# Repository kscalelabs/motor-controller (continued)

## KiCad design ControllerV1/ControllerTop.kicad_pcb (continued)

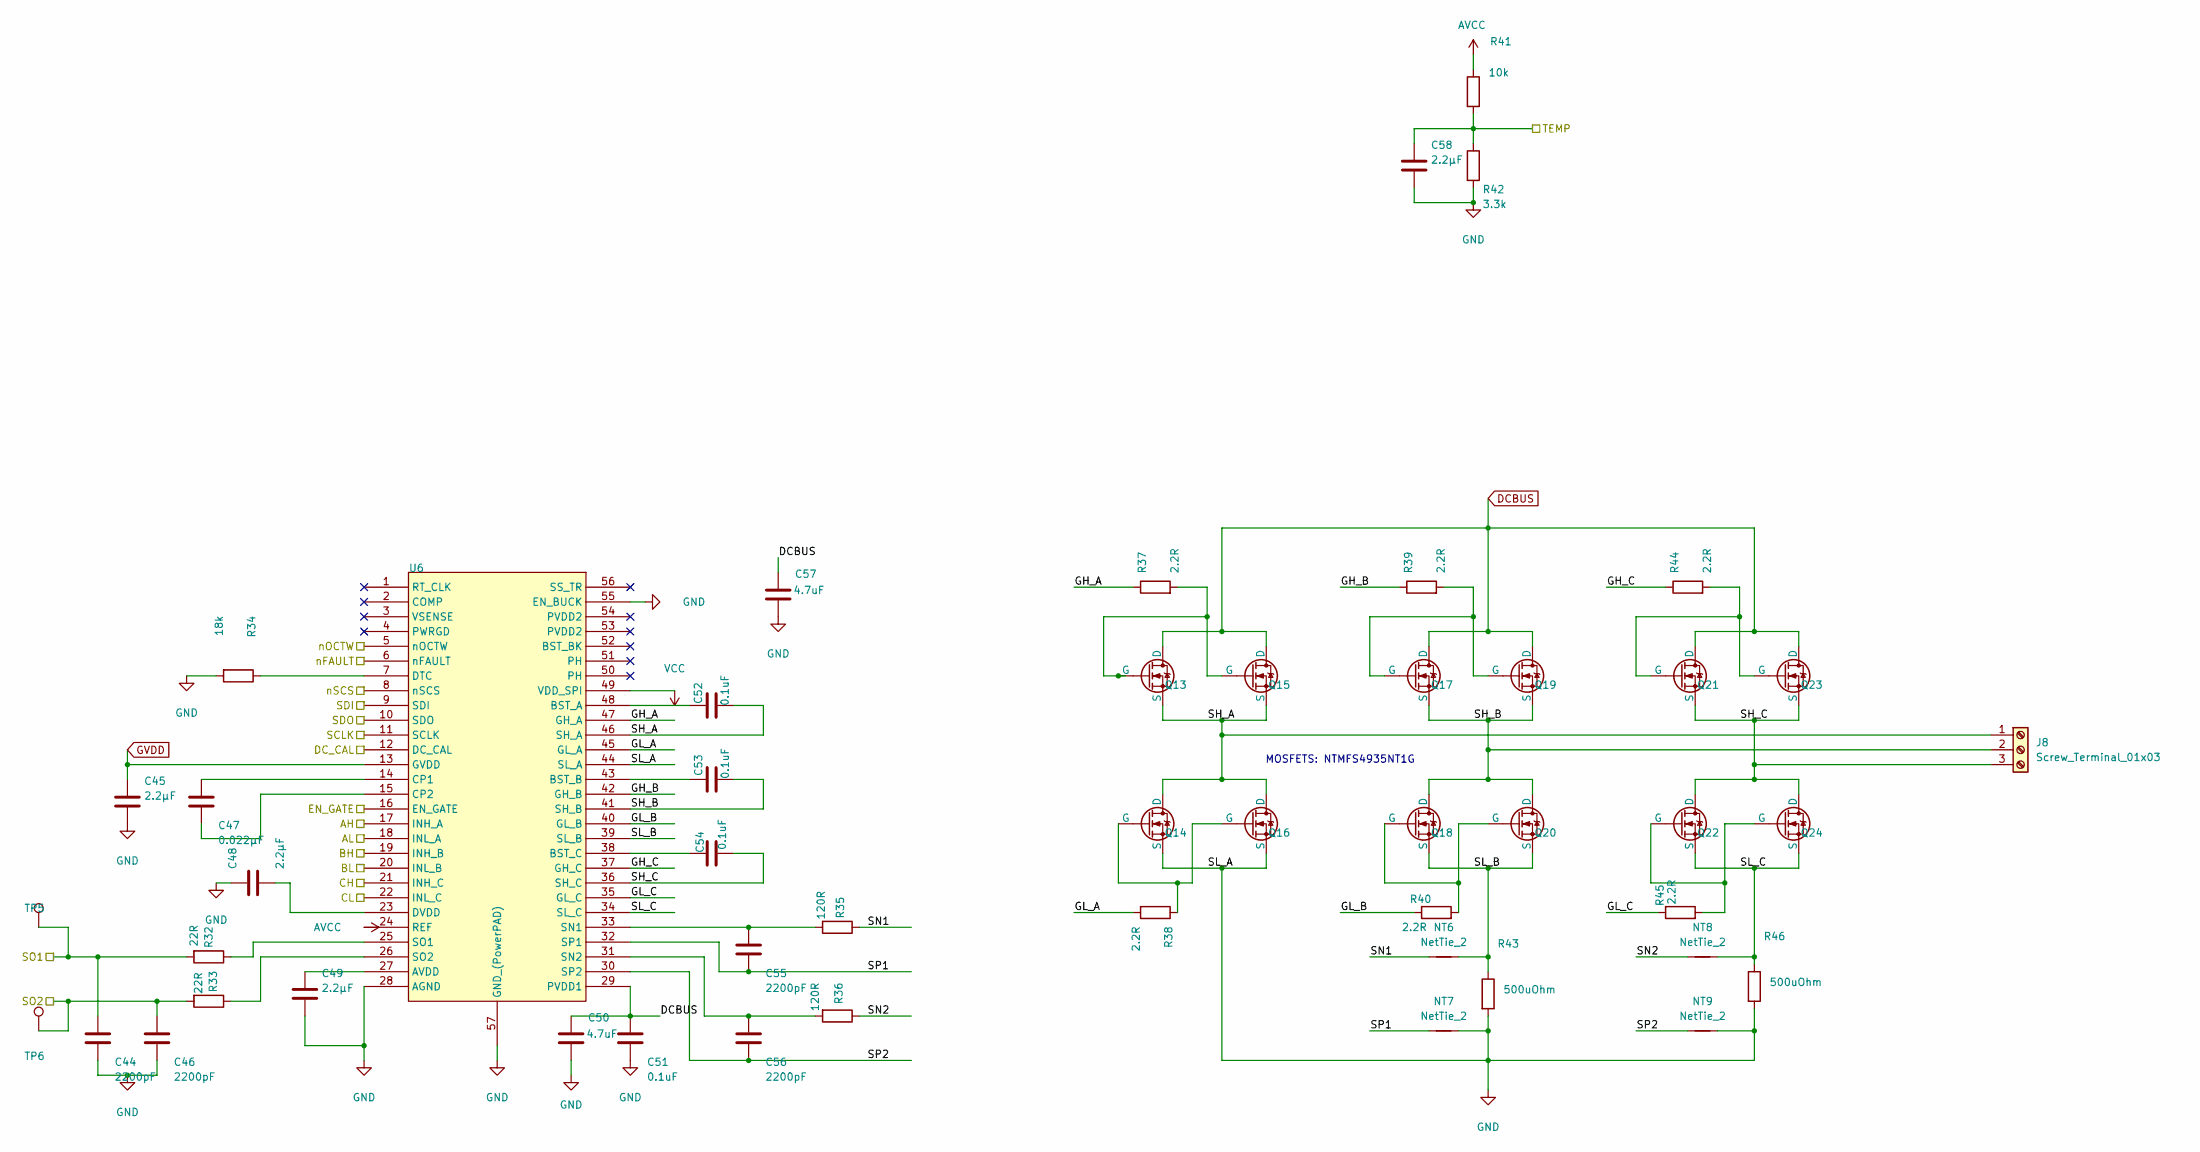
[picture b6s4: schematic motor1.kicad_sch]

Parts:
C44, C46, C55, C56: 2200pF; C_0603_1608Metric; TOLERANCE ±5%; VOLTAGE - RATED 50V; PART STATUS Active
C45, C48, C49, C58: 2.2µF; C_0603_1608Metric; TOLERANCE ±10%; VOLTAGE - RATED 16V; MANUFACTURER PART NUMBER GRM188R61C225KE15D
C47: 0.022µF; C_0603_1608Metric; TOLERANCE ±10%; VOLTAGE - RATED 50V; MANUFACTURER PART NUMBER GRM188R71H223KA01D
C50, C57: 4.7uF; C_0805_2012Metric; TOLERANCE ±10%; VOLTAGE - RATED 35V; PART STATUS Active
C51, C52, C53, C54: 0.1uF; C_0603_1608Metric; TOLERANCE ±10%; VOLTAGE - RATED 50V; MANUFACTURER PART NUMBER GRM188R71H104KA93D
J8: Screw_Terminal_01x03; TerminalBlock_MetzConnect_Type011_RT05503HBWC_1x03_P5.00mm_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
NT6, NT7, NT8, NT9: NetTie_2; NetTie-2_SMD_Pad0.5mm
Q13, Q14, Q16, Q17, Q18, Q20, Q21, Q22, Q24: ONSemi_SO-8FL_488AA; DRIVE VOLTAGE (MAX RDS 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 4.5V, 10V; PART STATUS Active
Q15, Q19, Q23: FILL_FOOTPRINT; ONSemi_SO-8FL_488AA; DRIVE VOLTAGE (MAX RDS 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 4.5V, 10V; PART STATUS Active
R32, R33: 22R; R_0603_1608Metric; TOLERANCE ±1%; MANUFACTURER PART NUMBER RC0603FR-0722RL
R34: 18k; R_0603_1608Metric; TOLERANCE ±1%; MANUFACTURER PART NUMBER RC0603FR-0718KL
R35, R36: 120R; R_0603_1608Metric; TOLERANCE ±1%; MANUFACTURER PART NUMBER RC0603FR-07120RL
R37, R38, R39, R40, R44, R45: 2.2R; R_0603_1608Metric; TOLERANCE ±1%; MANUFACTURER PART NUMBER RC0603FR-072R2L
R41: 10k; R_0402_1005Metric
R42: 3.3k; R_0603_1608Metric; TOLERANCE ±1%; MANUFACTURER PART NUMBER RC0603FR-073K3L
R43, R46: 500uOhm; R_2512_6332Metric; TOLERANCE ±1%; PART STATUS Active
TP5, TP6: TESTPOINT; TestPoint_Pad_1.0x1.0mm
U6: HTSSOP-56-1EP_6.1x14mm_P0.5mm_EP3.61x6.35mm

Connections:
/EN_GATE: U6.16 (EN_GATE); also elsewhere on the board
/M1_AH: U6.17 (INH_A); also elsewhere on the board
/M1_AL: U6.18 (INL_A); also elsewhere on the board
/M1_BH: U6.19 (INH_B); also elsewhere on the board
/M1_BL: U6.20 (INL_B); also elsewhere on the board
/M1_CH: U6.21 (INH_C); also elsewhere on the board
/M1_CL: U6.22 (INL_C); also elsewhere on the board
/M1_DC_CAL: U6.12 (DC_CAL); also elsewhere on the board
/M1_NCS: U6.8 (nSCS); also elsewhere on the board
/M1_SO1: C44.1, R32.2, TP5.1; also elsewhere on the board
/M1_SO2: C46.1, R33.2, TP6.1; also elsewhere on the board
/M1_TEMP: C58.1, R41.2, R42.1, U6.5 (nOCTW); also elsewhere on the board
/Motor 1/GH_A: R37.1, U6.47 (GH_A)
/Motor 1/GH_B: R39.1, U6.42 (GH_B)
/Motor 1/GH_C: R44.1, U6.37 (GH_C)
/Motor 1/GL_A: R38.2, U6.45 (GL_A)
/Motor 1/GL_B: R40.1, U6.40 (GL_B)
/Motor 1/GL_C: R45.1, U6.35 (GL_C)
/Motor 1/SH_A: C52.1, J8.1, Q13.1 (S), Q14.5 (D), Q15.1 (S), Q16.5 (D), U6.46 (SH_A)
/Motor 1/SH_B: C53.2, J8.2, Q17.1 (S), Q18.5 (D), Q19.1 (S), Q20.5 (D), U6.41 (SH_B)
/Motor 1/SH_C: C54.2, J8.3, Q21.1 (S), Q22.5 (D), Q23.1 (S), Q24.5 (D), U6.36 (SH_C)
/Motor 1/SL_B: NT6.2, Q18.1 (S), Q20.1 (S), R43.1, U6.39 (SL_B)
/Motor 1/SL_C: NT8.2, Q22.1 (S), Q24.1 (S), R46.1, U6.34 (SL_C)
/Motor 1/SN1: NT6.1, R35.1
/Motor 1/SN2: NT8.1, R36.1
/Motor 1/SP1: C55.2, NT7.1, U6.32 (SP1)
/Motor 1/SP2: C56.2, NT9.1, U6.30 (SP2)
/SPI_MISO: U6.10 (SDO); also elsewhere on the board
/SPI_MOSI: U6.9 (SDI); also elsewhere on the board
/SPI_SCK: U6.11 (SCLK); also elsewhere on the board
/nFAULT: U6.6 (nFAULT); also elsewhere on the board
AVCC: R41.1, U6.24 (REF); also elsewhere on the board
DCBUS: C50.1, C51.1, C57.1, Q13.5 (D), Q15.5 (D), Q17.5 (D), Q19.5 (D), Q21.5 (D), Q23.5 (D), U6.29 (PVDD1); also elsewhere on the board
GND: C44.2, C45.2, C46.2, C48.1, C49.2, C50.2, C51.2, C57.2, C58.2, NT7.2, NT9.2, Q14.1 (S), Q16.1 (S), R34.2, R42.2, R43.2, R46.2, U6.28 (AGND), U6.44 (SL_A), U6.55 (EN_BUCK), U6.57 (GND_(PowerPAD)); also elsewhere on the board
GVDD: C45.1, U6.13 (GVDD); also elsewhere on the board
unnamed: Q13.4 (G), Q15.4 (G), R37.2
unnamed: Q14.4 (G), Q16.4 (G), R38.1
unnamed: Q17.4 (G), Q19.4 (G), R39.2
unnamed: Q18.4 (G), Q20.4 (G), R40.2
unnamed: Q21.4 (G), Q23.4 (G), R44.2
unnamed: Q22.4 (G), Q24.4 (G), R45.2
unnamed: C49.1, U6.27 (AVDD)
unnamed: C52.2, U6.48 (BST_A)
unnamed: C53.1, U6.43 (BST_B)
unnamed: C54.1, U6.38 (BST_C)
unnamed: C47.1, U6.14 (CP1)
unnamed: C47.2, U6.15 (CP2)
unnamed: R34.1, U6.7 (DTC)
unnamed: C48.2, U6.23 (DVDD)
unnamed: C55.1, R35.2, U6.33 (SN1)
unnamed: C56.1, R36.2, U6.31 (SN2)
unnamed: R32.1, U6.25 (SO1)
unnamed: R33.1, U6.26 (SO2)
VCC: U6.49 (VDD_SPI); also elsewhere on the board

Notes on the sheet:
MOSFETS: NTMFS4935NT1G

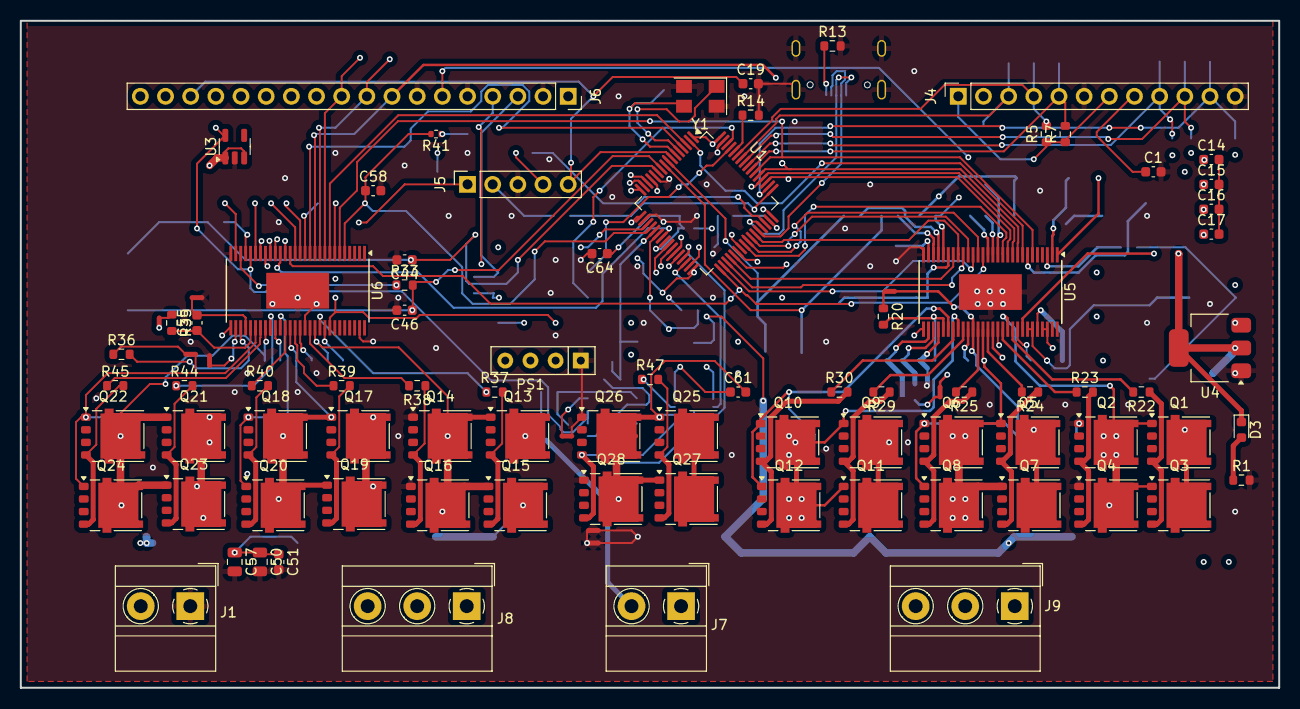
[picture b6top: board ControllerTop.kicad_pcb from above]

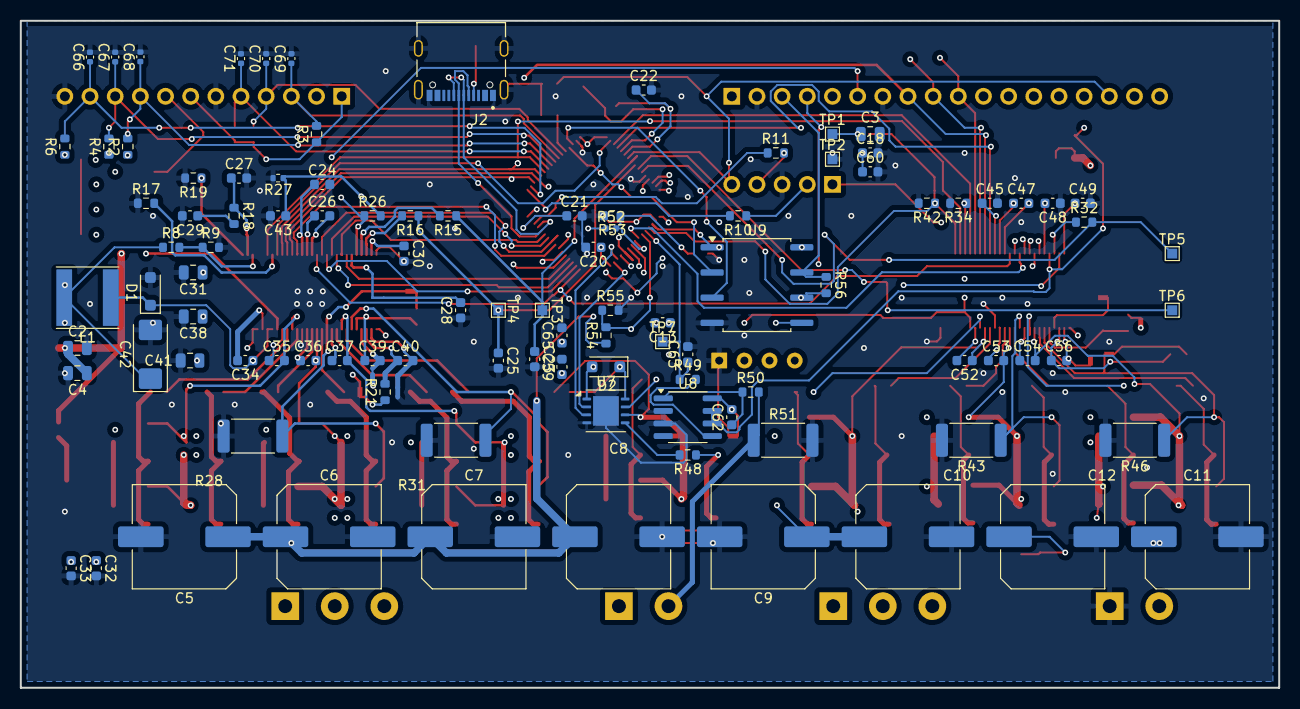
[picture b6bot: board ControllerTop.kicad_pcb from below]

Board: 4 copper layers, 127.0 x 67.3 mm, 194 parts (104 on the bottom side), 153 nets.

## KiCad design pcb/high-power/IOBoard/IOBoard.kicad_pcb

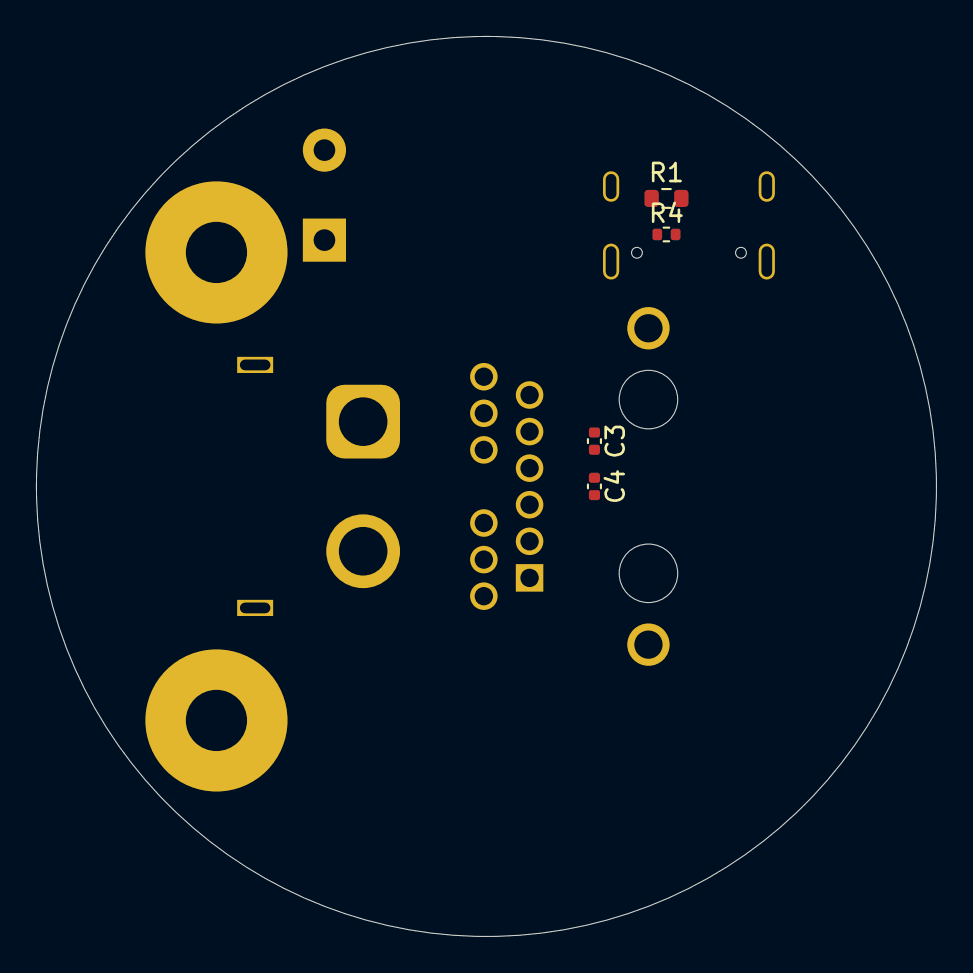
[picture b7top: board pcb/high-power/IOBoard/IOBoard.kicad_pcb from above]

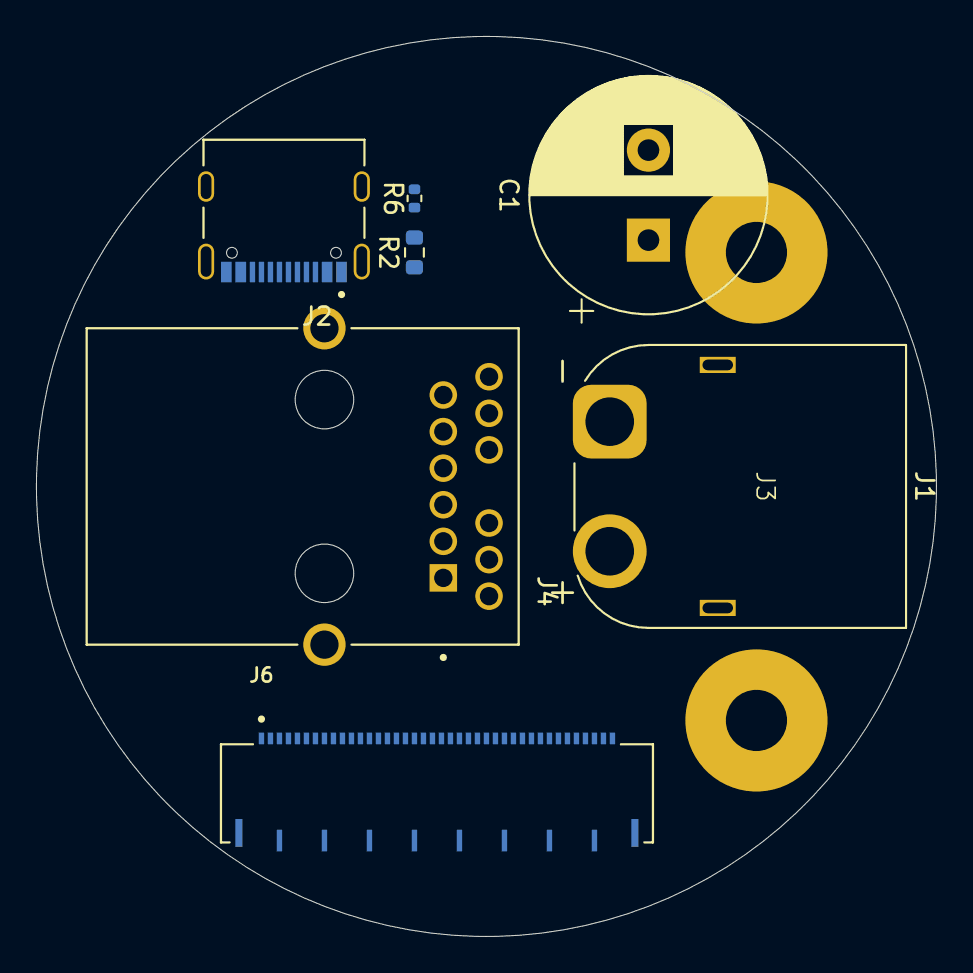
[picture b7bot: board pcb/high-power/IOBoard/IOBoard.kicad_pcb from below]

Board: 4 copper layers, 50.0 x 50.0 mm, 12 parts (8 on the bottom side), 19 nets, no tracks yet.

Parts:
C1: 100V 330uF; CP_Radial_D13.0mm_P5.00mm
C3, C4: 10pF; C_0402_1005Metric
J1: XT60PW-M; AMASS_XT60PW-M_1x02_P7.20mm_Horizontal
J2: TYPE-C-31-M-12; HRO_TYPE-C-31-M-12
J3: Mounting holes; Dual Post
J4: DNP; BEL_L8AL-1X1T-32A
J6: FH41-40S-0.5SH_05_; HRS_FH41-40S-0.5SH_05_
R1, R2: 5.1k; R_0603_1608Metric
R4, R6: 22R; R_0402_1005Metric

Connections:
/ETH0_CT1: C3.2, J4.6 (TRCT2), J4.12 (TRCT1), J6.12, J6.18
/ETH0_RXN: J4.10 (TRD1-), J6.14
/ETH0_RXP: J4.11 (TRD1+), J6.10
/ETH0_TXN: J4.5 (TRD2-), J6.20
/ETH0_TXP: J4.4 (TRD2+), J6.16
/ETH1_CT1: C4.2, J4.1 (TRCT3), J4.7 (TRCT4), J6.28, J6.34
/ETH1_RXN: J4.2 (TRD3-), J6.30
/ETH1_RXP: J4.3 (TRD3+), J6.26
/ETH1_TXN: J4.9 (TRD4-), J6.36
/ETH1_TXP: J4.8 (TRD4+), J6.32
/USB_DM: J2.A7 (DN1), J6.6, R4.2
/USB_DP: J2.A6 (DP1), J6.4, R6.2
DCBUS: C1.1, J1.1, J3.1
GND: C1.2, C3.1, C4.1, J1.2, J2.A1_B12 (GND), J2.B1_A12 (GND), J3.2, J6.1, J6.2, J6.3, J6.5, J6.7, J6.8, J6.9, J6.11, J6.13, J6.15, J6.17, J6.19, J6.21, J6.22, J6.23, J6.24, J6.25, J6.27, J6.29, J6.31, J6.33, J6.35, J6.37, J6.39, J6.40, R1.2, R2.2
unnamed: J2.A5 (CC1), R1.1
unnamed: J2.B5 (CC2), R2.1
unnamed: J2.B7 (DN2), R4.1
unnamed: J2.B6 (DP2), R6.1
SHIELD: J2.S1 (SHIELD), J2.S2 (SHIELD), J2.S3 (SHIELD), J2.S4 (SHIELD), J4.S1 (SHIELD), J4.S2 (SHIELD), J6.41 (GND), J6.42 (GND), J6.43 (GND), J6.44 (GND), J6.45 (GND), J6.46 (GND), J6.47 (GND), J6.48 (GND), J6.49 (GND), J6.50 (GND)

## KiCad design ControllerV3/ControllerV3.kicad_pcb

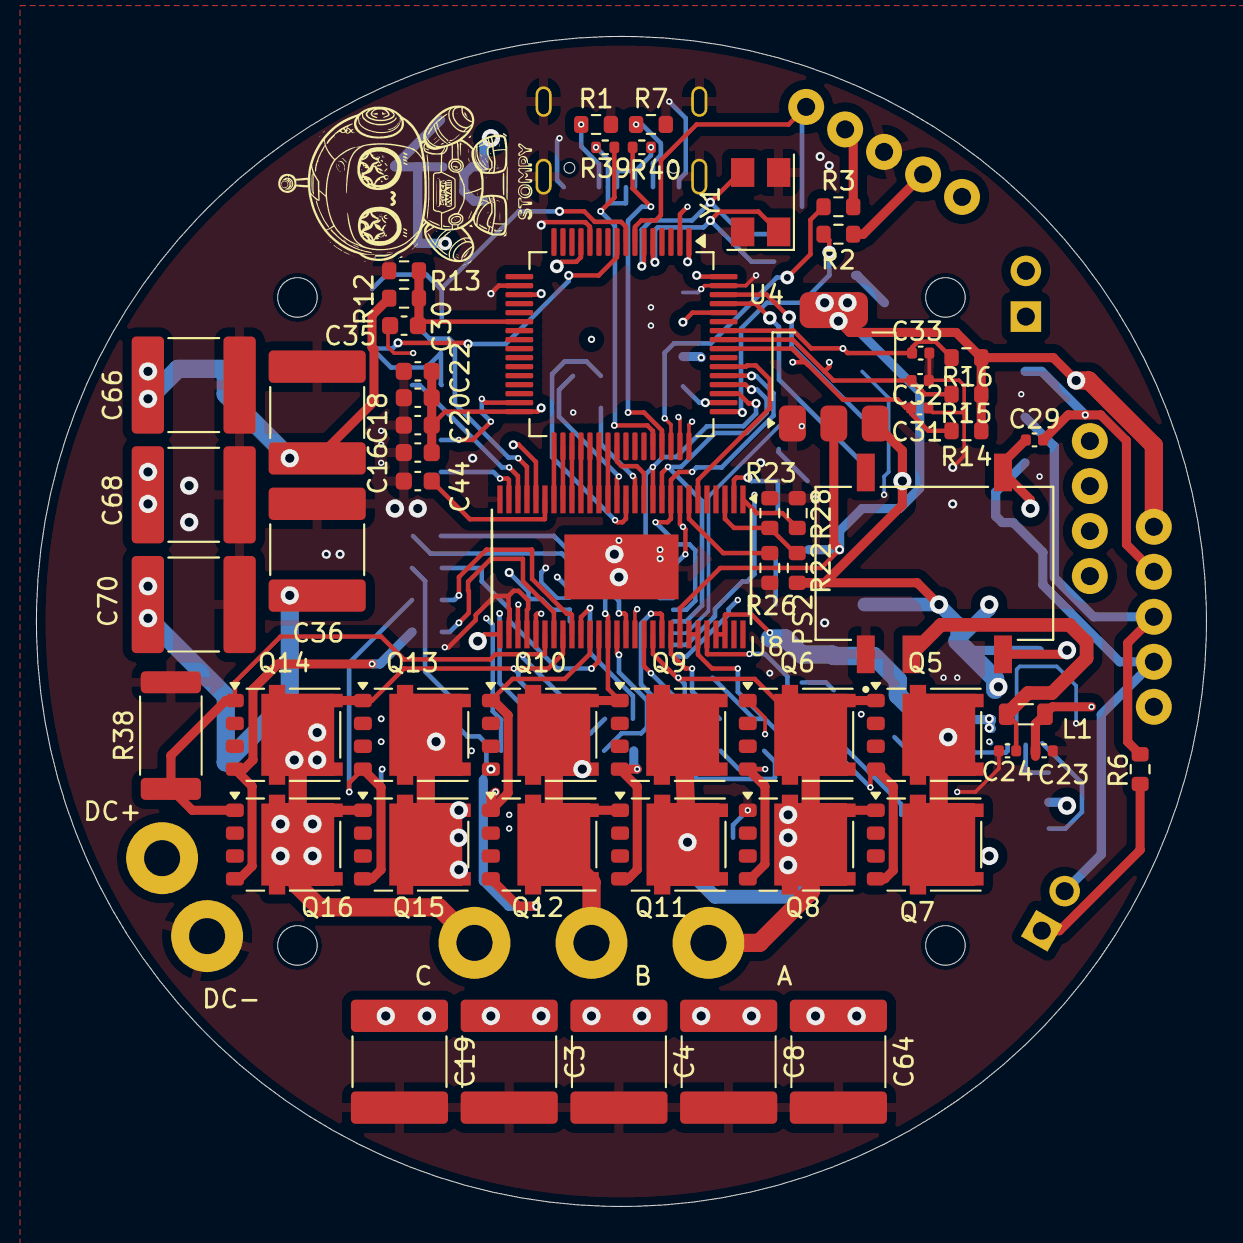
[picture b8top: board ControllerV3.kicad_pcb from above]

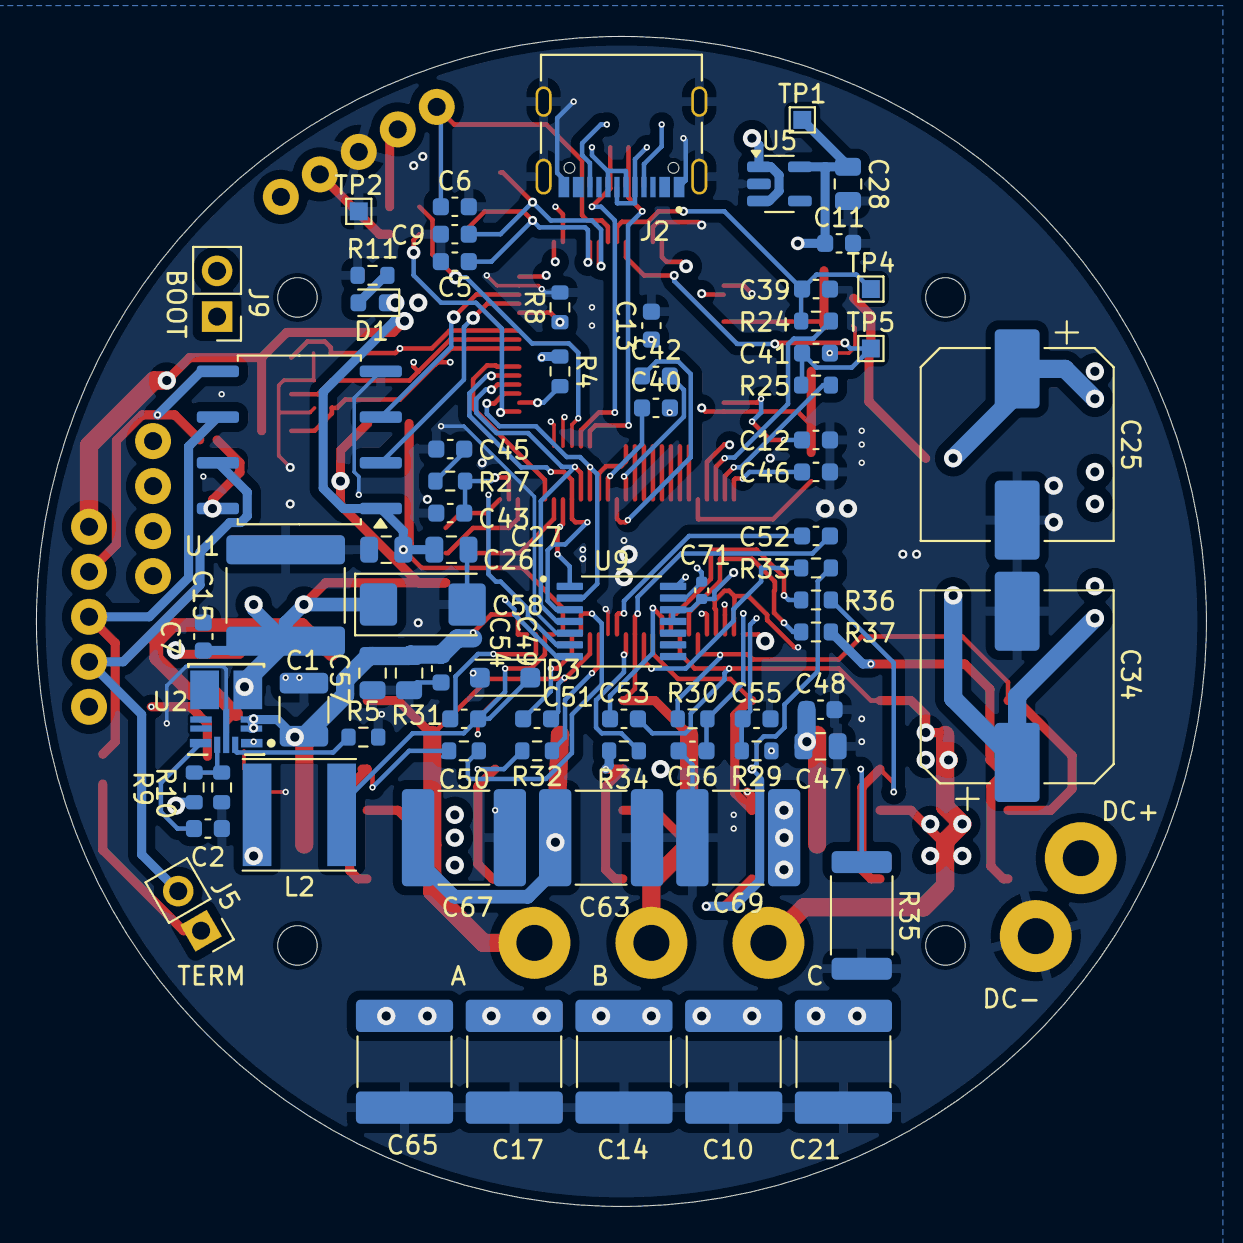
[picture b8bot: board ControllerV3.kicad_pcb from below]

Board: 4 copper layers, 65.0 x 65.0 mm, 141 parts (75 on the bottom side), 89 nets.

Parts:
C1: 2.2uF; C_1210_3225Metric
C2: 1uF; C_0603_1608Metric
C3, C4, C8, C10, C14, C17, C19, C21, C35, C36, C63, C64, C65, C66, C67, C68, C69, C70: 470uF; C_2220_5750Metric
C5, C9: 10pF; C_0603_1608Metric
C6, C11, C16, C18, C20, C22, C48, C49, C50, C51, C52, C53: 0.1uF; C_0603_1608Metric
C7, C12, C13, C30, C40, C44, C46: 2.2µF; C_0603_1608Metric
C15: 22uf; C_2225_5664Metric
C23, C24: 4.7uF; C_0402_1005Metric
C25, C34: 120uF; CP_Elec_10x10.5
C26, C27, C28, C47, C54, C57: 4.7uF; C_0805_2012Metric
C29: 10uF; C_0402_1005Metric
C31, C32, C33: 22nF; C_0402_1005Metric
C39, C41, C55, C56: 2200pF; C_0603_1608Metric
C42: 0.022µF; C_0603_1608Metric
C43: 82pF; C_0603_1608Metric
C45: 270pF; C_0603_1608Metric
C58: 68uF; CP_EIA-6032-28_Kemet-C
C71: 100nF; C_0402_1005Metric
D1: LTST-C190KGKT; D_0603_1608Metric
D3: D; D_SOD-123F
H1, H2, H3, H4: MountingHole; MountingHole_2.2mm_M2
J1: Screw_Terminal_01x02; Two-Hole
J2: TYPE-C-31-M-12; HRO_TYPE-C-31-M-12
J3, J8: Conn_01x05_Socket; Five-Hole
J5, J9: Conn_01x02_Pin; PinHeader_1x02_P2.54mm_Vertical
J7: Screw_Terminal_01x03; Three-Hole
J10: Conn_01x04_Socket; Nine-Hole
L1: 6.8uH; L_0805_2012Metric
L2: 22uH; L_Taiyo-Yuden_NR-60xx
PS2: B0505XT-1WR3-TR; CONV_B0505XT-1WR3-TR
Q5, Q6, Q7, Q8, Q9, Q10, Q11, Q12, Q13, Q14, Q15, Q16: ONSemi_SO-8FL_488AA
R1, R7: 5.1k; R_0603_1608Metric
R2, R3, R24, R25: 22R; R_0603_1608Metric
R4, R10: 10k; R_0603_1608Metric
R5: 11.3k; R_0603_1608Metric
R6, R29, R30: 120R; R_0603_1608Metric
R8, R27: 47K; R_0603_1608Metric
R9: 40.2k; R_0603_1608Metric
R11, R13: 1k; R_0603_1608Metric
R12: 18K; R_0603_1608Metric
R14, R15, R16, R23: 3.3k; R_0603_1608Metric
R22, R26: 18k; R_0603_1608Metric
R28: 220k; R_0603_1608Metric
R31, R32, R33, R34, R36, R37: 2.2R; R_0603_1608Metric
R35, R38: 500uOhm; R_2512_6332Metric
R39, R40: 22R; R_0402_1005Metric
TP1, TP2, TP4, TP5: TESTPOINT; TestPoint_Pad_1.0x1.0mm
U1: ISO1050DUB; SOP-8_6.62x9.15mm_P2.54mm
U2: TPSM365R6FRDNR; RDN0011A-MFG
U3: STM32F405RGTx; LQFP-64_10x10mm_P0.5mm
U4: LDL1117S33R; SOT-223
U5: LP5907MFX-3.3_NOPB; SOT-23-5
U8: HTSSOP-56-1EP_6.1x14mm_P0.5mm_EP3.61x6.35mm
U9: AS5047P-ATSM; SOP65P640X120-14N
Y1: ABM3B-8.000MHZ-10-1-U-T; Crystal_SMD_5032-4Pin_5.0x3.2mm

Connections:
5V: C7.1, C15.1, C23.1, C58.1, J8.1, L1.1, L2.2, R9.1, R22.1, U2.4 (VOUT), U4.3 (VIN), U5.1 (IN), U5.3 (EN)
/BOOT0: J9.1, R8.1, U3.60 (BOOT0)
/CAN_D: U1.3 (TXD), U3.62 (PB9)
/CAN_H: J5.2, J8.2, U1.7 (CANH)
/CAN_L: J8.3, R6.2, U1.6 (CANL)
/CAN_R: U1.2 (RXD), U3.61 (PB8)
/EN_GATE: U3.39 (PC8), U8.16 (EN_GATE)
/M0_AH: U3.38 (PC7), U8.17 (INH_A)
/M0_AL: U3.37 (PC6), U8.18 (INL_A)
/M0_BH: U3.36 (PB15), U8.19 (INH_B)
/M0_BL: U3.35 (PB14), U8.20 (INL_B)
/M0_CH: U3.34 (PB13), U8.21 (INH_C)
/M0_CL: U3.33 (PB12), U8.22 (INL_C)
/M0_DC_CAL: U3.40 (PC9), U8.12 (DC_CAL)
/M0_ENC_A: C31.1, R14.2, U3.56 (PB4), U9.14 (I/PWM)
/M0_ENC_B: C32.1, R15.2, U3.57 (PB5), U9.6 (B)
/M0_ENC_Z: C33.1, R16.2, U3.58 (PB6), U9.7 (A)
/M0_SO1: C39.1, R24.1, TP4.1, U3.8 (PC0)
/M0_SO2: C41.1, R25.1, TP5.1, U3.9 (PC1)
/Motor 0/GH_A: R31.2, U8.47 (GH_A)
/Motor 0/GH_B: R34.2, U8.42 (GH_B)
/Motor 0/GH_C: R36.2, U8.37 (GH_C)
/Motor 0/GL_A: R32.1, U8.45 (GL_A)
/Motor 0/GL_B: R33.2, U8.40 (GL_B)
/Motor 0/GL_C: R37.1, U8.35 (GL_C)
/Motor 0/SH_A: C51.2, J7.1, Q5.1 (S), Q6.5 (D), Q7.1 (S), Q8.5 (D), U8.46 (SH_A)
/Motor 0/SH_B: C52.2, J7.2, Q9.1 (S), Q10.5 (D), Q11.1 (S), Q12.5 (D), U8.41 (SH_B)
/Motor 0/SH_C: C53.2, J7.3, Q13.1 (S), Q14.5 (D), Q15.1 (S), Q16.5 (D), U8.36 (SH_C)
/Motor 0/SL_B: Q10.1 (S), Q12.1 (S), R29.1, R35.1, U8.39 (SL_B)
/Motor 0/SL_C: Q14.1 (S), Q16.1 (S), R30.1, R38.1, U8.34 (SL_C)
/NRST: C6.1, J3.5, U3.7 (NRST)
/PGOOD: R4.2, U2.1 (PGOOD), U3.50 (PA15)
/SPI_CS: J10.1, U3.2 (PC13), U8.8 (nSCS), U9.1 (CSN)
/SPI_MISO: J10.3, U3.52 (PC11), U8.10 (SDO), U9.4 (MOSI)
/SPI_MOSI: J10.4, U3.53 (PC12), U8.9 (SDI), U9.3 (MISO)
/SPI_SCK: J10.2, U3.51 (PC10), U8.11 (SCLK), U9.2 (CLK)
/SWCLK: R2.2, U3.49 (PA14)
/SWDIO: R3.1, U3.46 (PA13)
/USB_DM: J2.A7 (DN1), J2.B7 (DN2), R39.2
/USB_DP: J2.A6 (DP1), J2.B6 (DP2), R40.2
/VBUS_S: C30.1, R12.2, R13.1, U3.22 (PA6)
/nFAULT: U3.54 (PD2), U8.6 (nFAULT)
AVCC: C11.1, C28.1, C71.1, TP1.1, U3.13 (VDDA), U5.5 (OUT), U8.24 (REF), U9.11 (VDD), U9.12 (VDD3V3)
DCBUS: C1.1, C3.1, C4.1, C8.1, C10.1, C14.1, C17.1, C19.1, C21.1, C25.1, C34.1, C35.1, C36.1, C47.1, C48.1, C49.1, C54.1, C57.1, C63.1, C64.1, C65.1, C66.1, C67.1, C68.1, C69.1, C70.1, J1.2, Q5.5 (D), Q7.5 (D), Q9.5 (D), Q11.5 (D), Q13.5 (D), Q15.5 (D), R12.1, U2.2 (EN), U2.3 (VIN), U8.29 (PVDD1), U8.53 (PVDD2), U8.54 (PVDD2)
GND: C1.2, C2.2, C3.2, C4.2, C5.2, C6.2, C7.2, C8.2, C9.2, C10.2, C11.2, C12.2, C13.2, C14.2, C15.2, C16.2, C17.2, C18.2, C19.2, C20.2, C21.2, C22.2, C23.2, C24.2, C25.2, C26.2, C27.2, C28.2, C30.2, C31.2, C32.2, C33.2, C34.2, C35.2, C36.2, C39.2, C40.2, C41.2, C43.2, C44.1, C45.2, C46.2, C47.2, C48.2, C49.2, C54.2, C55.2, C56.2, C57.2, C58.2, C63.2, C64.2, C65.2, C66.2, C67.2, C68.2, C69.2, C70.2, C71.2, D3.2 (A), J1.1, J2.A1_B12 (GND), J2.B1_A12 (GND), J2.S1 (SHIELD), J2.S2 (SHIELD), J2.S3 (SHIELD), J2.S4 (SHIELD), J3.3, PS2.1 (GND), Q6.1 (S), Q8.1 (S), R1.2, R5.2, R7.2, R8.2, R10.2, R11.2, R13.2, R23.2, R26.1, R28.2, R35.2, R38.2, TP2.1, U1.4 (GND1), U2.10 (GND), U3.12 (VSSA), U3.18 (VSS), U3.63 (VSS), U4.1 (GND), U5.2 (GND), U8.28 (AGND), U8.30 (SP2), U8.32 (SP1), U8.44 (SL_A), U8.57 (GND_(PowerPAD)), U9.5 (TEST), U9.13 (GND), Y1.2 (GND), Y1.4 (GND)
GVDD: C40.1, U8.13 (GVDD)
I-5V: C29.1, PS2.5 (+VO), U1.8 (VCC2)
IGND: C29.2, J8.4, PS2.4 (0V), U1.5 (GND2)
unnamed: C45.1, R27.2
unnamed: D1.2, R11.1
unnamed: C50.1, D3.1 (K), L2.1, U8.50 (PH), U8.51 (PH)
unnamed: J2.A5 (CC1), R1.1
unnamed: J2.B5 (CC2), R7.1
unnamed: J3.2, R2.1
unnamed: J3.4, R3.2
unnamed: J5.1, R6.1
unnamed: C24.1, L1.2, PS2.2 (VIN)
unnamed: Q5.4 (G), Q7.4 (G), R31.1
unnamed: Q6.4 (G), Q8.4 (G), R32.2
unnamed: Q10.4 (G), Q12.4 (G), R33.1
unnamed: Q9.4 (G), Q11.4 (G), R34.1
unnamed: Q13.4 (G), Q15.4 (G), R36.1
unnamed: Q14.4 (G), Q16.4 (G), R37.2
unnamed: R9.2, R10.1, U2.9 (BIAS)
unnamed: R5.1, U2.11 (MODE_SYNC)
unnamed: C2.1, U2.8 (VCC)
unnamed: R39.1, U3.44 (PA11)
unnamed: R40.1, U3.45 (PA12)
unnamed: C5.1, U3.5 (PH0), Y1.1
unnamed: C9.1, U3.6 (PH1), Y1.3
unnamed: C12.1, U3.31 (VCAP_1)
unnamed: C13.1, U3.47 (VCAP_2)
unnamed: C46.1, U8.27 (AVDD)
unnamed: C51.1, U8.48 (BST_A)
unnamed: C52.1, U8.43 (BST_B)
unnamed: C50.2, U8.52 (BST_BK)
unnamed: C53.1, U8.38 (BST_C)
unnamed: C43.1, R27.1, U8.2 (COMP)
unnamed: C42.1, U8.14 (CP1)
unnamed: C42.2, U8.15 (CP2)
unnamed: R26.2, U8.7 (DTC)
unnamed: C44.2, U8.23 (DVDD)
unnamed: R28.1, U8.1 (RT_CLK)
unnamed: C55.1, R29.2, U8.33 (SN1)
unnamed: C56.1, R30.2, U8.31 (SN2)
unnamed: R24.2, U8.25 (SO1)
unnamed: R25.2, U8.26 (SO2)
unnamed: R22.2, R23.1, U8.3 (VSENSE)
VCC: C16.1, C18.1, C20.1, C22.1, C26.1, C27.1, D1.1, J3.1, J8.5, J9.2, R4.1, R14.1, R15.1, R16.1, U1.1 (VCC1), U3.1 (VBAT), U3.19 (VDD), U3.32 (VDD), U3.48 (VDD), U3.64 (VDD), U4.2 (VOUT), U4.4 (VOUT), U8.49 (VDD_SPI)

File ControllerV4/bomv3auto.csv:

Designator,Footprint,Quantity,Value,LCSC Part #
C1,1210,1,2.2uF,C840133
"C10, C14, C17, C19, C21, C3, C35, C36, C4, C63, C64, C65, C66, C67, C68, C69, C70, C8",2220,18,22uF,C784103
"C11, C16, C18, C20, C22, C48, C49, C50, C51, C52, C53, C6",603,12,0.1uF,
"C12, C13, C30, C40, C44, C46, C7",603,7,2.2uF,C2859193
C15,2225,1,22uf,C882503
C2,603,1,1uF,
"C23, C24",402,2,4.7uF,
"C25, C34",CP_Elec_10x10.5,2,120uF,C487157
"C26, C27, C28, C47, C54, C57",805,6,4.7uF,C2897302
C29,402,1,10uF,
"C31, C32, C33",402,3,22nF,
"C39, C41, C55, C56",603,4,2200pF,
C42,603,1,0.022µF,
C43,603,1,82pF,
C45,603,1,270pF,
"C5, C9",603,2,10pF,
C58,CP_EIA-6032-28_Kemet-C,1,68uF,C7220
C71,402,1,100nF,
D1,603,1,LTST-C190KGKT,C125094
D3,D_SOD-123F,1,D,C43381
J1,Two-Hole,1,,
J10,Nine-Hole,1,,
J2,HRO_TYPE-C-31-M-12,1,TYPE-C-31-M-12,C165948
"J3, J8",Five-Hole,2,,
"J5, J9",PinHeader_1x02_P2.54mm_Vertical,2,Conn_01x02_Pin,C124375
J7,Three-Hole,1,,
L1,805,1,6.8uH,C486332
L2,L_Taiyo-Yuden_NR-60xx,1,22uH,C45737
PS2,CONV_B0505XT-1WR3-TR,1,B0505XT-1WR3-TR,C19188495
"Q10, Q11, Q12, Q13, Q14, Q15, Q16, Q5, Q6, Q7, Q8, Q9",ONSemi_SO-8FL_488AA,12,~,C348543
"R1, R7",603,2,5.1k,
"R10, R4",603,2,10k,
"R11, R13",603,2,1k,
"R12, R22, R26",603,3,18K,
"R14, R15, R16, R23",603,4,3.3k,
"R2, R24, R25, R3",603,4,22R,
"R27, R8",603,2,47K,
R28,603,1,220k,
"R29, R30, R6",603,3,120R,
"R31, R32, R33, R34, R36, R37",603,6,2.2R,
"R35, R38",2512,2,500uOhm,C500733
"R39, R40",402,2,22R,
R5,603,1,11.3k,
R9,603,1,40.2k,
"TP1, TP2, TP4, TP5",TestPoint_Pad_1.0x1.0mm,4,TESTPOINT,
U1,SOP-8_6.62x9.15mm_P2.54mm,1,ISO1050DUBR,C16428
U2,RDN0011A-MFG,1,TPSM365R6FRDNR,C6723000
U3,LQFP-64_10x10mm_P0.5mm,1,STM32F405RGT6,C15742
U4,SOT-223,1,LDL1117S33R,C435835
U5,SOT-23-5,1,LP5907MFX-3.3_NOPB,C80670
U8,HTSSOP-56-1EP_6.1x14mm_P0.5mm_EP3.61x6.35mm,1,~,C98969
U9,SOP65P640X120-14N,1,AS5047P-ATSM,C962063
Y1,Crystal_SMD_5032-4Pin_5.0x3.2mm,1,ABM3B-8.000MHZ-10-1-U-T,C1985378

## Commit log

2024-06-18 Initial Commit with Rev 1-3
2024-06-18 Add README
2024-06-26 Added temporary v4 changes
2024-06-26 Renamed aux
2024-06-26 renamed all aux and fix file pathing error
2024-06-28 added gitignore
2024-06-28 Initial folder structure changes for etherCAT
2024-07-01 added initial files for ethercat design
2024-07-02 Initial design without Ethernet connectors
2024-07-03 Added IO Board project
2024-07-03 checkpoint commit
2024-07-03 schematic finished, need to set proper ERCs
2024-07-04 fix all ERCs
2024-07-06 Added more BOM items
2024-07-08 checkpoint
2024-07-09 Renamed folder names
2024-07-09 added low power variant with single mosfet
2024-07-10 IO Board for LP variant finished
2024-07-10 remove locks
2024-07-12 Checkpoint changes before switching to XMC4800
2024-07-13 Finished new 2+2 IOboard
2024-07-17 Added XMC4800
2024-07-25 Added Ethernet PHY
2024-07-26 added stm32 variant back
2024-07-27 starting HP version
2024-07-30 stash before via stitching
2024-07-31 finished with HP controller
2024-07-31 production files
2024-07-31 diffs
2024-08-06 redid layout and mounting
2024-08-07 fix part number
2024-08-08 added drc exclusions
2024-08-09 fixed bom
2024-08-29 Added docs and errata
